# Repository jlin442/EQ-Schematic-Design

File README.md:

# EQ-Schematic-Design

This was a parametric EQ designed by R.G. Keen on this website: http://www.geofex.com/article_folders/eqs/paramet.htm. 

The PCB was designed using EAGLE based on the existing schematic.

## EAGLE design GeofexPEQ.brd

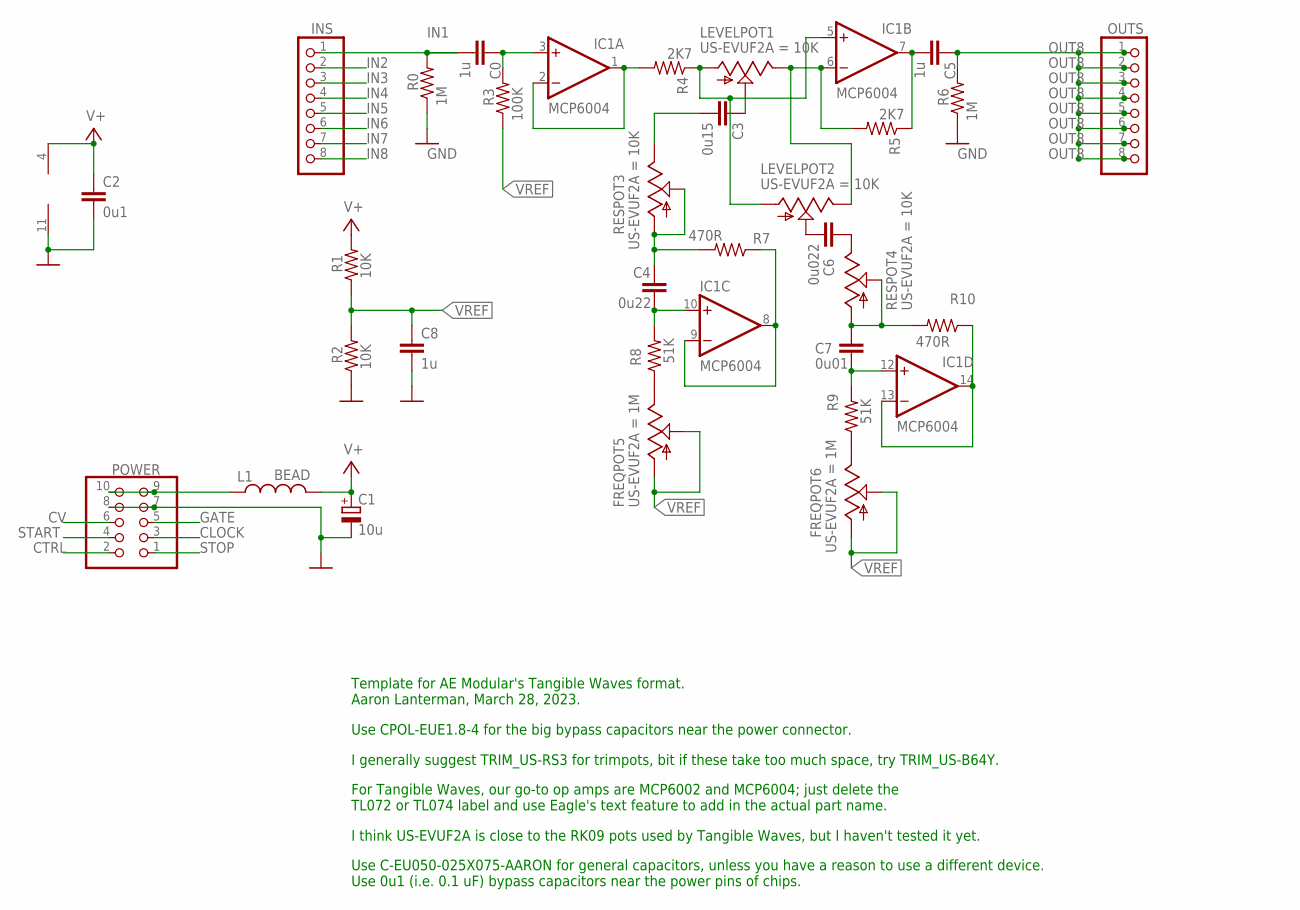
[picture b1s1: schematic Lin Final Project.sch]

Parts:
C0, C5, C8: 1u; C050-025X075-AARON
C1: 10u; E1,8-4
C2: 0u1; C050-025X075-AARON
C3: 0u15; C050-025X075-AARON
C4: 0u22; C050-025X075-AARON
C6: 0u022; C050-025X075-AARON
C7: 0u01; C050-025X075-AARON
FREQPOT5, FREQPOT6: US-EVUF2A; EVUF
IC1: TL074P; DIL14
INS: PINHD-1X8; 1X08
L1: BEAD; 0207/10
LEVELPOT1, LEVELPOT2: US-EVUF2A; EVUF
OUTS: PINHD-1X8; 1X08
POWER: PINHD-2X5; 2X05
R0, R6: 1M; 0207/10
R1, R2: 10K; 0207/10
R3: 100K; 0207/10
R4, R5: 2K7; 0207/10
R7, R10: 470R; 0207/10
R8, R9: 51K; 0207/10
RESPOT3, RESPOT4: US-EVUF2A; EVUF

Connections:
+5V: L1.1, POWER.9, POWER.10
CLOCK: POWER.3
CTRL: POWER.2
CV: POWER.6
GATE: POWER.5
GND: C1.-, C2.2, C8.2, IC1.11 (V-), POWER.7, POWER.8, R0.1, R2.1, R6.1
IN1: C0.2, INS.1, R0.2
IN2: INS.2
IN3: INS.3
IN4: INS.4
IN5: INS.5
IN6: INS.6
IN7: INS.7
IN8: INS.8
unnamed: C0.1, IC1.3 (+IN), R3.2
unnamed: IC1.1 (OUT), IC1.2 (-IN), R4.2
unnamed: C3.1, LEVELPOT1.2 (S)
unnamed: C4.1, R7.2, RESPOT3.1 (A), RESPOT3.2 (S)
unnamed: C3.2, RESPOT3.3 (E)
unnamed: IC1.6 (-IN), LEVELPOT1.3 (E), LEVELPOT2.3 (E), R5.2
unnamed: C6.2, LEVELPOT2.2 (S)
unnamed: C5.2, IC1.7 (OUT), R5.1
unnamed: C6.1, RESPOT4.3 (E)
unnamed: C7.1, R10.2, RESPOT4.1 (A), RESPOT4.2 (S)
unnamed: IC1.8 (OUT), IC1.9 (-IN), R7.1
unnamed: FREQPOT5.3 (E), R8.1
unnamed: C4.2, IC1.10 (+IN), R8.2
unnamed: IC1.13 (-IN), IC1.14 (OUT), R10.1
unnamed: C7.2, IC1.12 (+IN), R9.2
unnamed: FREQPOT6.3 (E), R9.1
unnamed: IC1.5 (+IN), LEVELPOT1.1 (A), LEVELPOT2.1 (A), R4.1
OUT8: C5.1, OUTS.1, OUTS.2, OUTS.3, OUTS.4, OUTS.5, OUTS.6, OUTS.7, OUTS.8, R6.2
START: POWER.4
STOP: POWER.1
V+: C1.+, C2.1, IC1.4 (V+), L1.2, R1.2
VREF: C8.1, FREQPOT5.1 (A), FREQPOT5.2 (S), FREQPOT6.1 (A), FREQPOT6.2 (S), R1.1, R2.2, R3.1

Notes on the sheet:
Template for AE Modular's Tangible Waves format. Aaron Lanterman, March 28, 2023.
Use CPOL-EUE1.8-4 for the big bypass capacitors near the power connector.
Use C-EU050-025X075-AARON for general capacitors, unless you have a reason to use a different device. Use 0u1 (i.e. 0.1 uF) bypass capacitors near the power pins of chips.
I generally suggest TRIM_US-RS3 for trimpots, bit if these take too much space, try TRIM_US-B64Y.
For Tangible Waves, our go-to op amps are MCP6002 and MCP6004; just delete the TL072 or TL074 label and use Eagle's text feature to add in the actual part name.
I think US-EVUF2A is close to the RK09 pots used by Tangible Waves, but I haven't tested it yet.

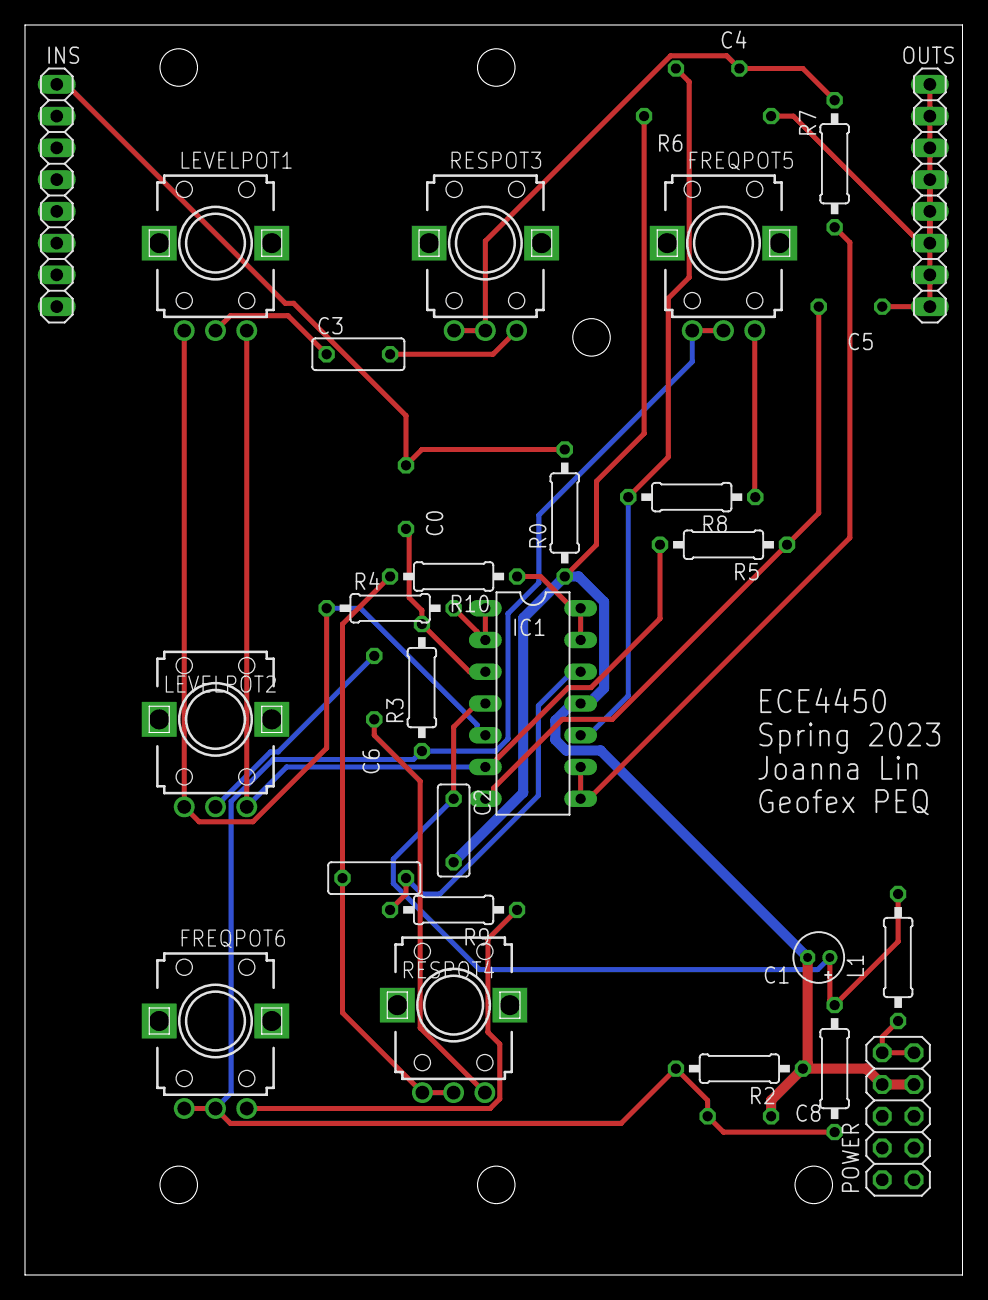
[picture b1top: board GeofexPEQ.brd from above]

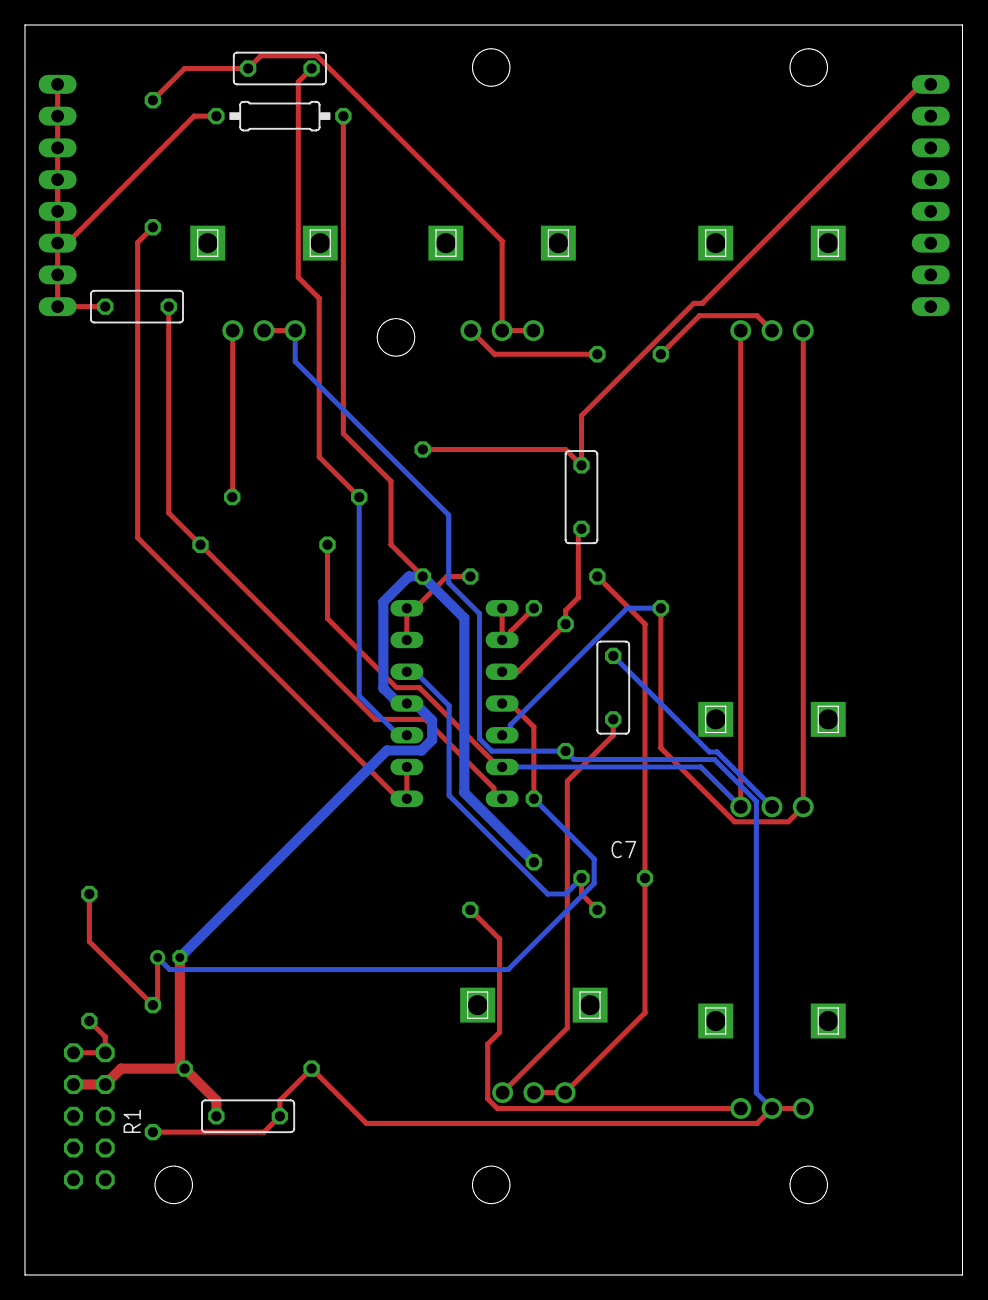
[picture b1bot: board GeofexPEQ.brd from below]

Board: 2 copper layers, 75.0 x 100.0 mm, 31 parts (6 on the bottom side), 23 nets.

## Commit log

2023-12-27 Rename Lin Final Project.brd to PCB.brd
